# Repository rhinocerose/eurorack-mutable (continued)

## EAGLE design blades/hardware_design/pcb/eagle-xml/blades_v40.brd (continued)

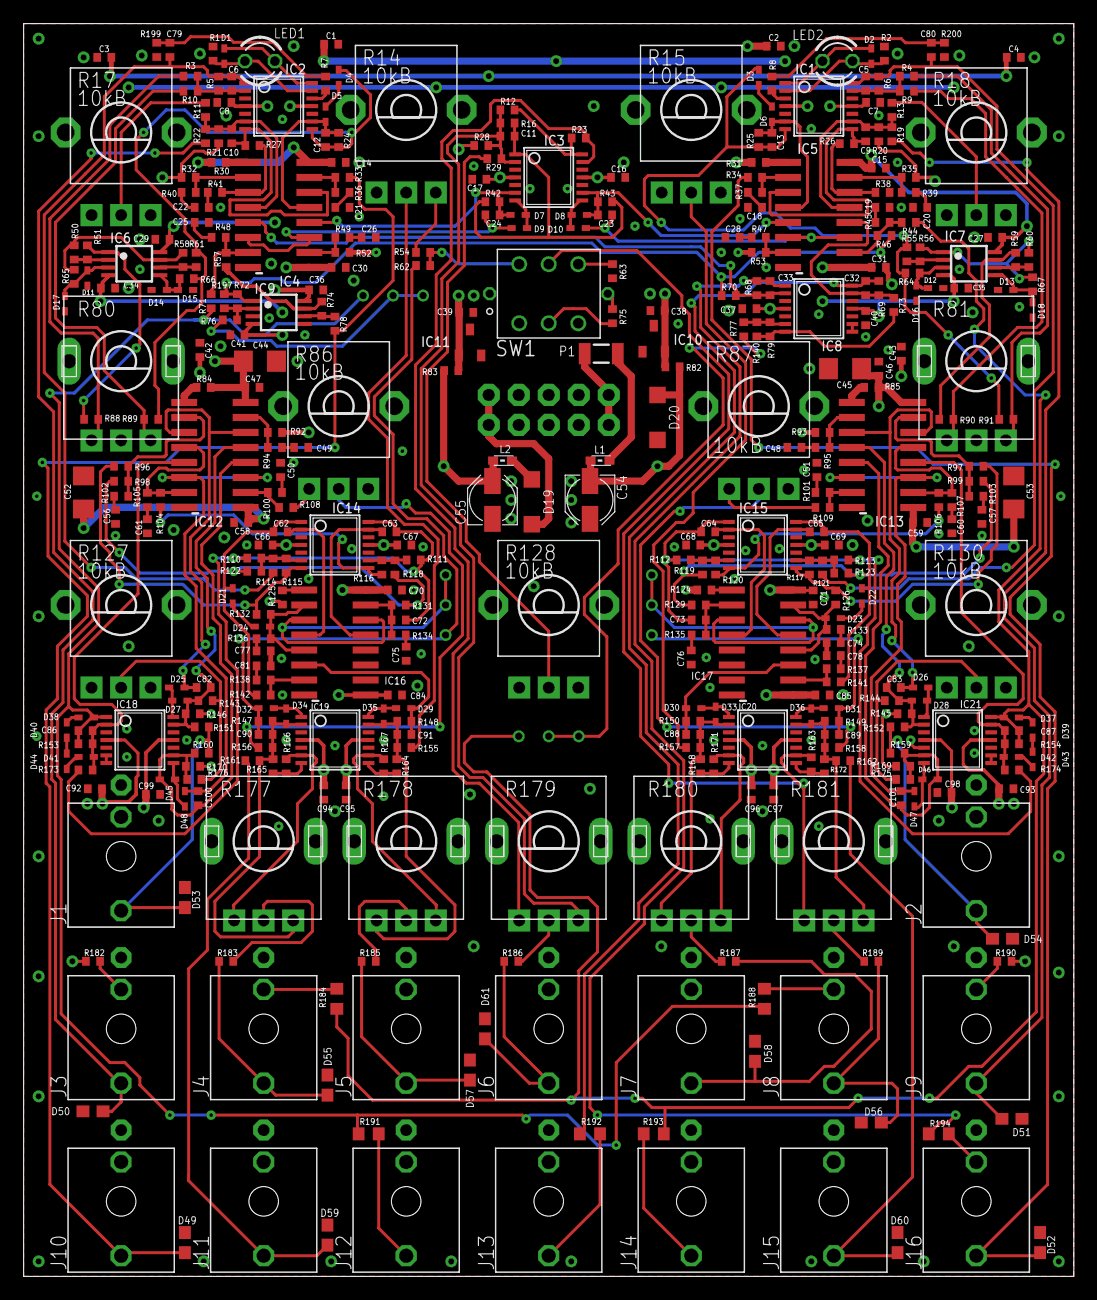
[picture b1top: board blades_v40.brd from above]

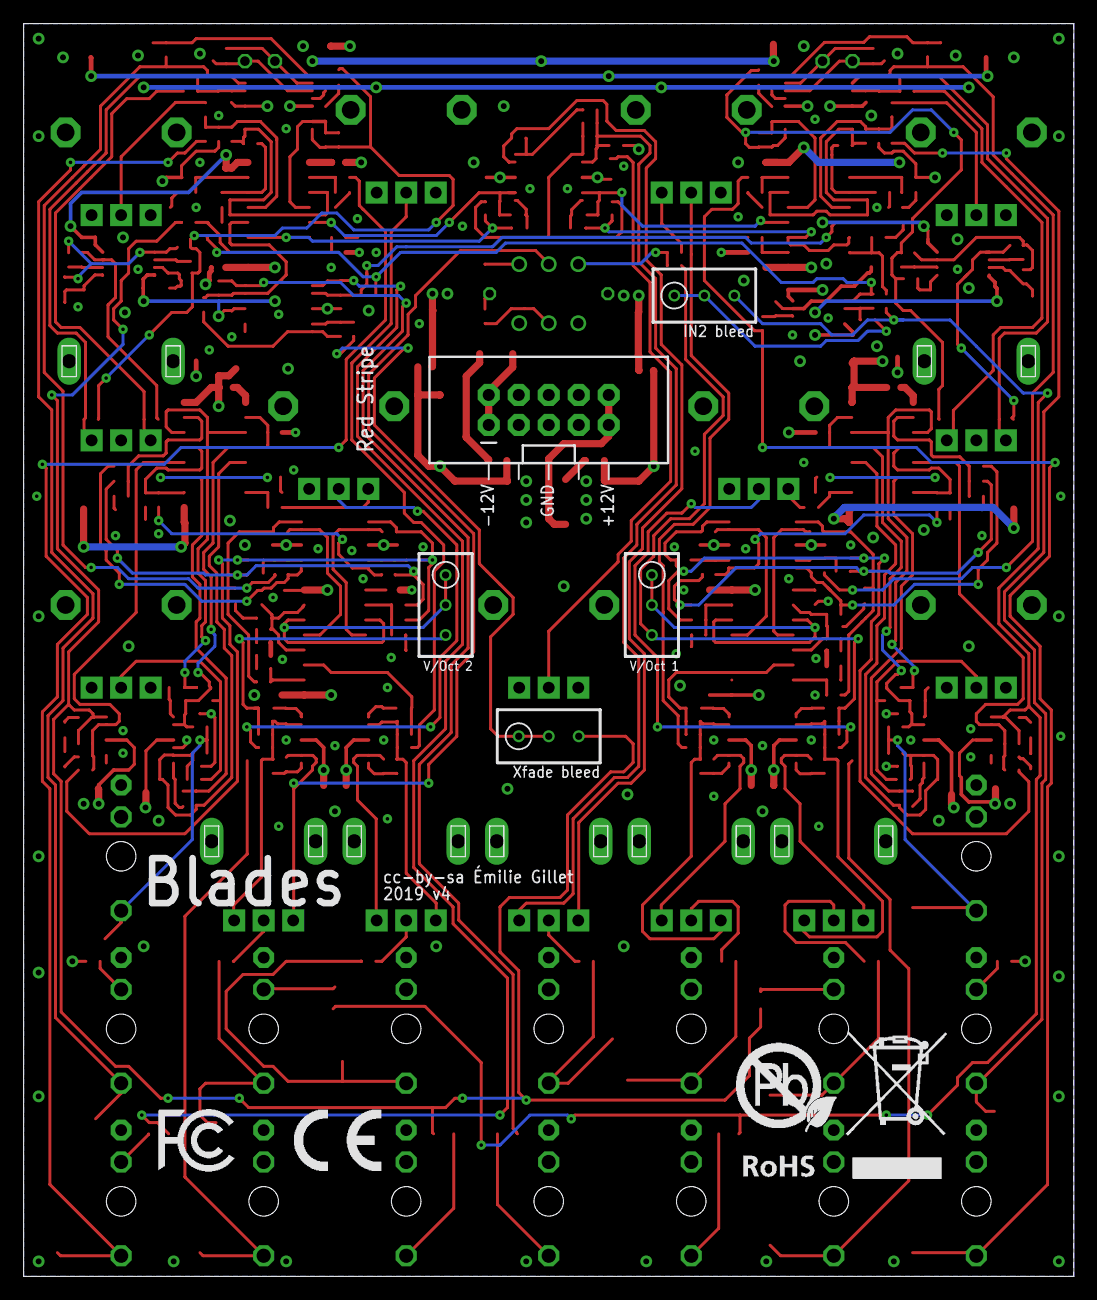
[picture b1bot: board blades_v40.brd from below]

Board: 4 copper layers, 88.9 x 106.0 mm, 409 parts (8 on the bottom side), 225 nets.

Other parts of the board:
U$1: ROHS_BIG
U$2: FCC_MEDIUM
U$3: CE_MEDIUM

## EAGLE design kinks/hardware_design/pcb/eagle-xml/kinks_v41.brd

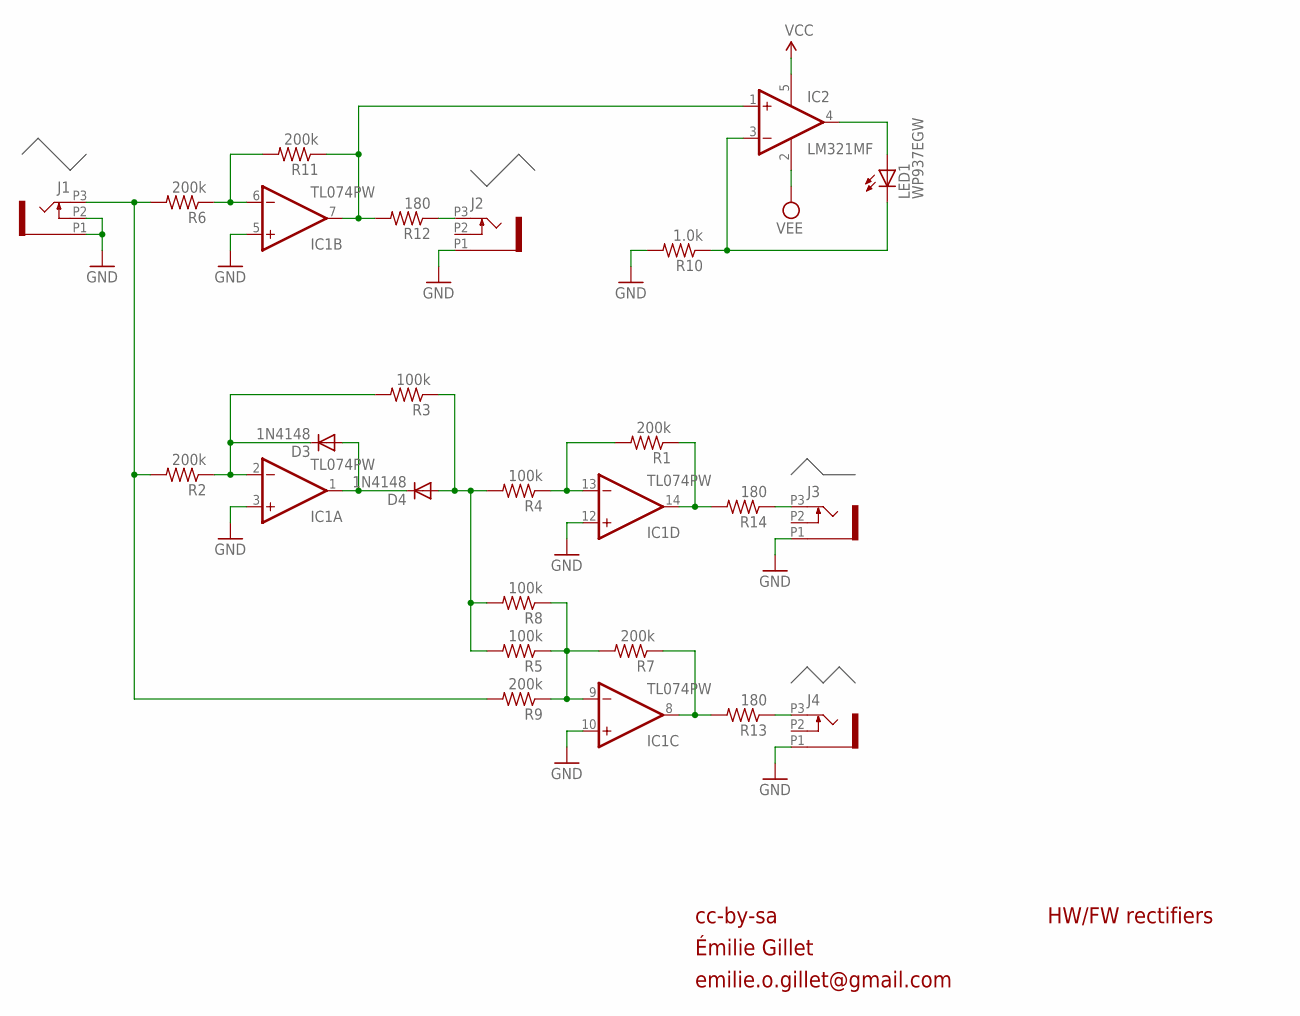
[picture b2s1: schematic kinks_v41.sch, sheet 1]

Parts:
D3, D4: 1N4148; SOD523
IC1: TL074PW; TSSOP14
IC2: LM321MF; SOT23-5
J1, J2, J3, J4: PJ301_THONKICONN6; WQP_PJ_301M6
LED1: WP937EGW; LED3MM
R1, R2, R6, R7, R9, R11: 200k; R0402
R3, R4, R5, R8: 100k; R0402
R10: 1.0k; R0402
R12, R13, R14: 180; R0402

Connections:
GND: IC1.3 (+IN), IC1.5 (+IN), IC1.10 (+IN), IC1.12 (+IN), J1.P1 (1), J1.P2 (2), J2.P1 (1), J3.P1 (1), J4.P1 (1), R10.2; also elsewhere on the board
unnamed: IC2.3 (-IN), LED1.K (C), R10.1
unnamed: IC2.4 (OUT), LED1.A
unnamed: IC1.6 (-IN), R6.1, R11.2
unnamed: IC1.7 (OUT), IC2.1 (+IN), R11.1, R12.2
unnamed: J2.P3 (3), R12.1
unnamed: D3.C, IC1.2 (-IN), R2.1, R3.2
unnamed: D3.A, D4.C, IC1.1 (OUT)
unnamed: IC1.14 (OUT), R1.1, R14.2
unnamed: IC1.13 (-IN), R1.2, R4.1
unnamed: J3.P3 (3), R14.1
unnamed: IC1.9 (-IN), R5.1, R7.2, R8.1, R9.1
unnamed: J4.P3 (3), R13.1
unnamed: IC1.8 (OUT), R7.1, R13.2
unnamed: J1.P3 (3), R2.2, R6.2, R9.2
unnamed: D4.A, R3.1, R4.2, R5.2, R8.2
VCC: IC2.5 (V+); also elsewhere on the board
VEE: IC2.2 (V-); also elsewhere on the board

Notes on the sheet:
cc-by-sa
HW/FW rectifiers
Émilie Gillet
emilie.o.gillet@gmail.com

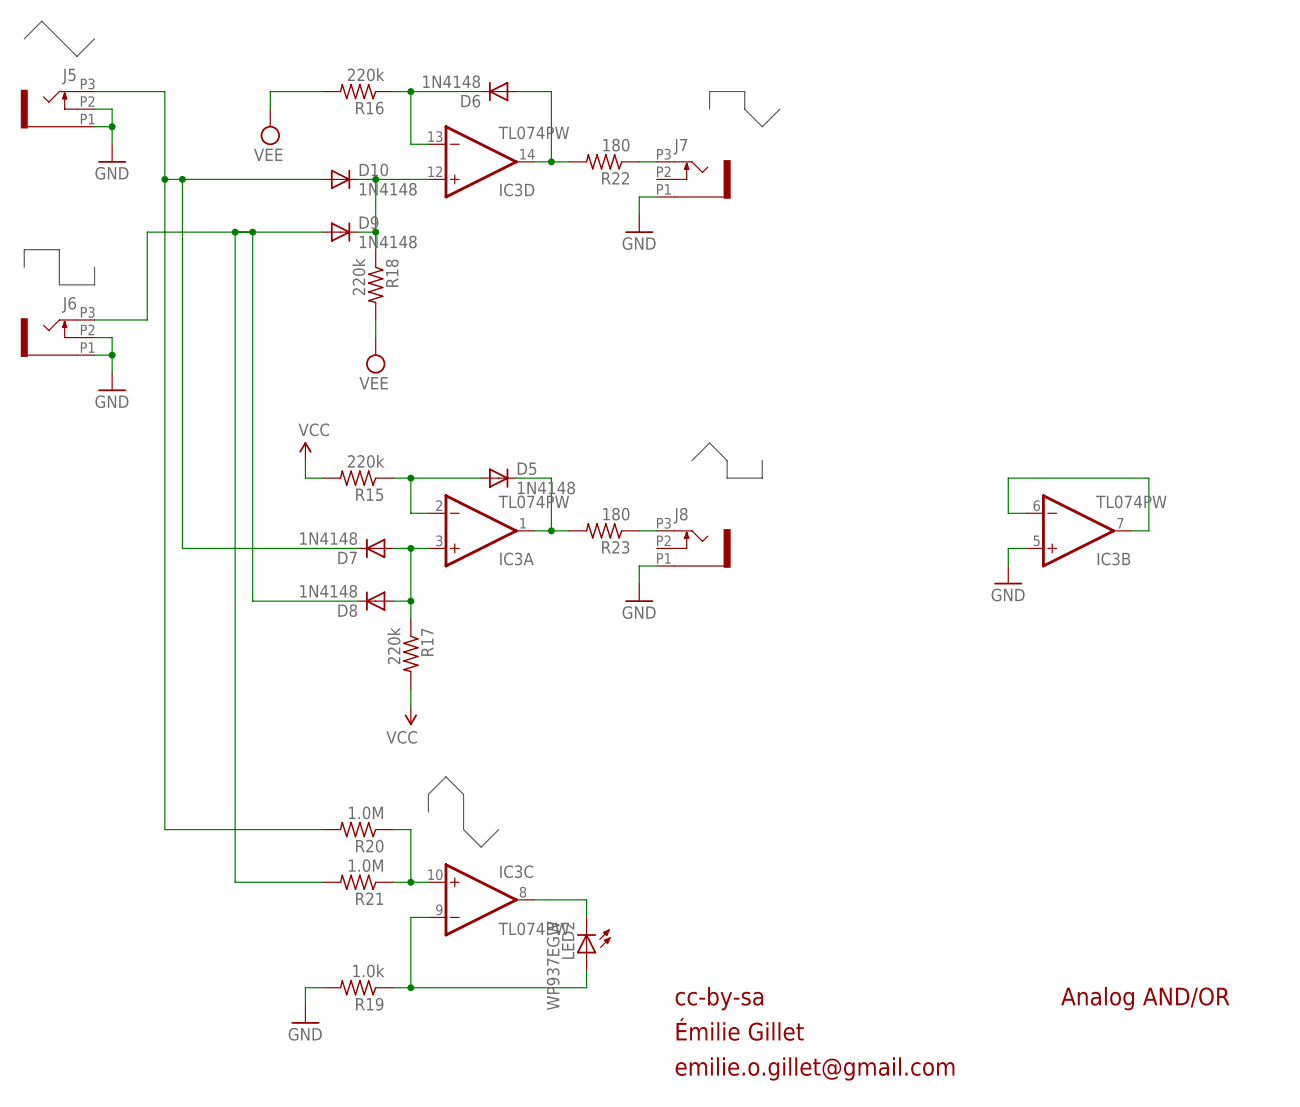
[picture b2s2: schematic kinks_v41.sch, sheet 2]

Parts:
D5, D6, D7, D8, D9, D10: 1N4148; SOD523
IC3: TL074PW; TSSOP14
J5, J6, J7, J8: PJ301_THONKICONN6; WQP_PJ_301M6
LED2: WP937EGW; LED3MM
R15, R16, R17, R18: 220k; R0402
R19: 1.0k; R0402
R20, R21: 1.0M; R0402
R22, R23: 180; R0402

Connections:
A: D7.C, D10.A, J5.P3 (3), R20.2
B: D8.C, D9.A, J6.P3 (3), R21.2
GND: IC3.5 (+IN), J5.P1 (1), J5.P2 (2), J6.P1 (1), J6.P2 (2), J7.P1 (1), J8.P1 (1), R19.2; also elsewhere on the board
unnamed: D9.C, D10.C, IC3.12 (+IN), R18.1
unnamed: D6.A, IC3.14 (OUT), R22.2
unnamed: D6.C, IC3.13 (-IN), R16.1
unnamed: D7.A, D8.A, IC3.3 (+IN), R17.1
unnamed: IC3.6 (-IN), IC3.7 (OUT)
unnamed: D5.C, IC3.1 (OUT), R23.2
unnamed: IC3.8 (OUT), LED2.K (C)
unnamed: D5.A, IC3.2 (-IN), R15.1
unnamed: J8.P3 (3), R23.1
unnamed: IC3.10 (+IN), R20.1, R21.1
unnamed: IC3.9 (-IN), LED2.A, R19.1
unnamed: J7.P3 (3), R22.1
VCC: R15.2, R17.2; also elsewhere on the board
VEE: R16.2, R18.2; also elsewhere on the board

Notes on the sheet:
cc-by-sa
Analog AND/OR
Émilie Gillet
emilie.o.gillet@gmail.com

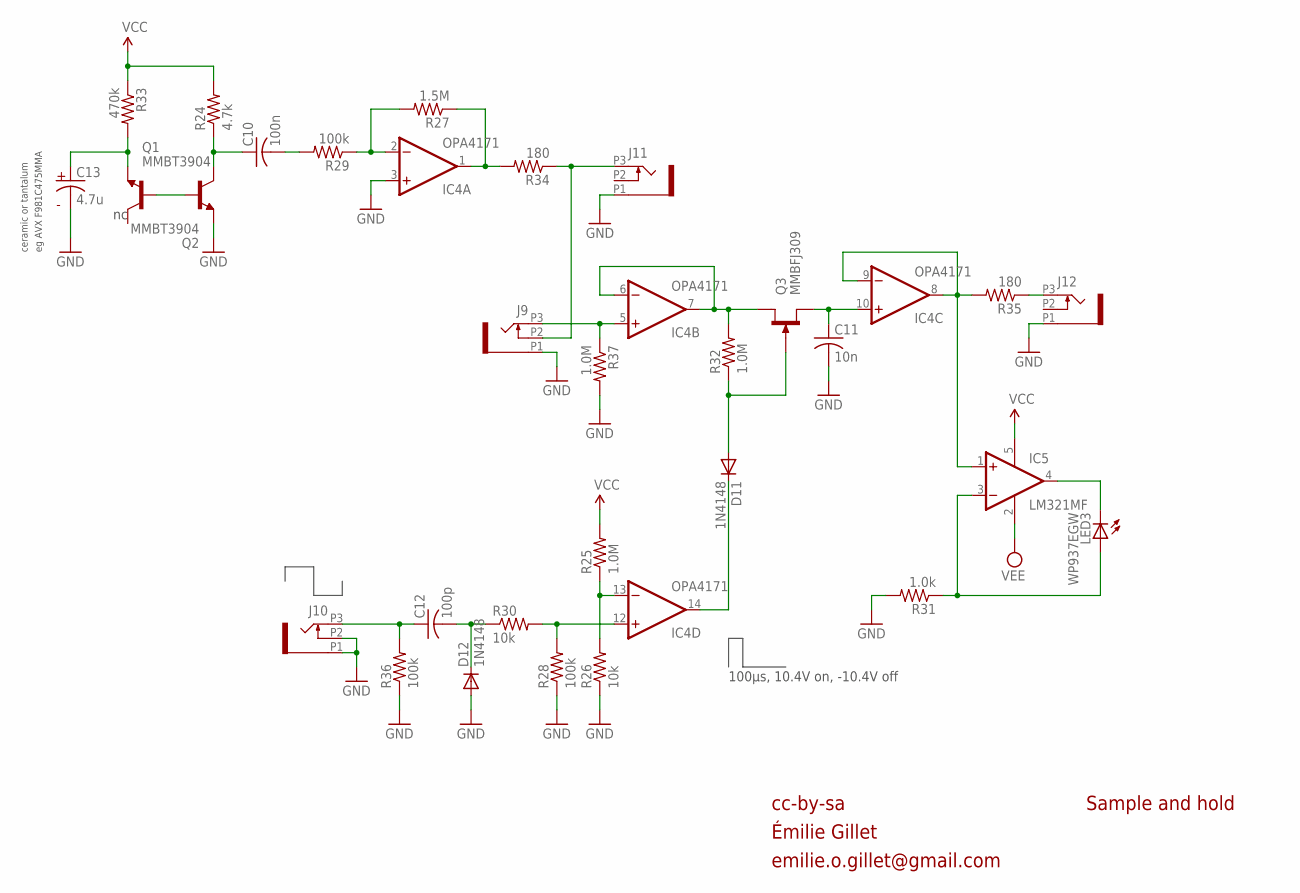
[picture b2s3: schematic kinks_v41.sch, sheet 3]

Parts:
C10: 100n; C0402
C11: 10n; C0603
C12: 100p; C0402
C13: 4.7u; C0603
D11, D12: 1N4148; SOD523
IC4: OPA4171; TSSOP14
IC5: LM321MF; SOT23-5
J9, J10, J11, J12: PJ301_THONKICONN6; WQP_PJ_301M6
LED3: WP937EGW; LED3MM
Q1, Q2: MMBT3904; SOT23-BEC
Q3: MMBFJ309; SOT23
R24: 4.7k; R0402
R25, R32, R37: 1.0M; R0402
R26, R30: 10k; R0402
R27: 1.5M; R0402
R28, R29, R36: 100k; R0402
R31: 1.0k; R0402
R33: 470k; R0402
R34, R35: 180; R0402

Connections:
GND: C11.2, C13.2, D12.A, IC4.3 (+IN), J9.P1 (1), J10.P1 (1), J10.P2 (2), J11.P1 (1), J12.P1 (1), Q1.E, R26.1, R28.1, R31.2, R36.1, R37.2; also elsewhere on the board
unnamed: IC4.8 (OUT), IC4.9 (-IN), IC5.1 (+IN), R35.2
unnamed: Q1.B, Q2.B
unnamed: C13.1, Q2.E, R33.2
unnamed: C10.2, R29.2
unnamed: IC4.2 (-IN), R27.2, R29.1
unnamed: IC5.3 (-IN), LED3.A, R31.1
unnamed: IC5.4 (OUT), LED3.K (C)
unnamed: C10.1, Q1.C, R24.1
unnamed: IC4.1 (OUT), R27.1, R34.2
unnamed: J9.P2 (2), J11.P3 (3), R34.1
unnamed: IC4.5 (+IN), J9.P3 (3), R37.1
unnamed: IC4.6 (-IN), IC4.7 (OUT), Q3.1 (D), R32.2
unnamed: D11.A, Q3.3 (G), R32.1
unnamed: D11.C, IC4.14 (OUT)
unnamed: C11.1, IC4.10 (+IN), Q3.2 (S)
unnamed: IC4.12 (+IN), R28.2, R30.2
unnamed: J12.P3 (3), R35.1
unnamed: C12.1, J10.P3 (3), R36.2
unnamed: IC4.13 (-IN), R25.1, R26.2
unnamed: C12.2, D12.C, R30.1
VCC: IC5.5 (V+), R24.2, R25.2, R33.1; also elsewhere on the board
VEE: IC5.2 (V-); also elsewhere on the board

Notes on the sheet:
cc-by-sa
Sample and hold
100µs, 10.4V on, -10.4V off
eg AVX F981C475MMA
ceramic or tantalum
Émilie Gillet
emilie.o.gillet@gmail.com

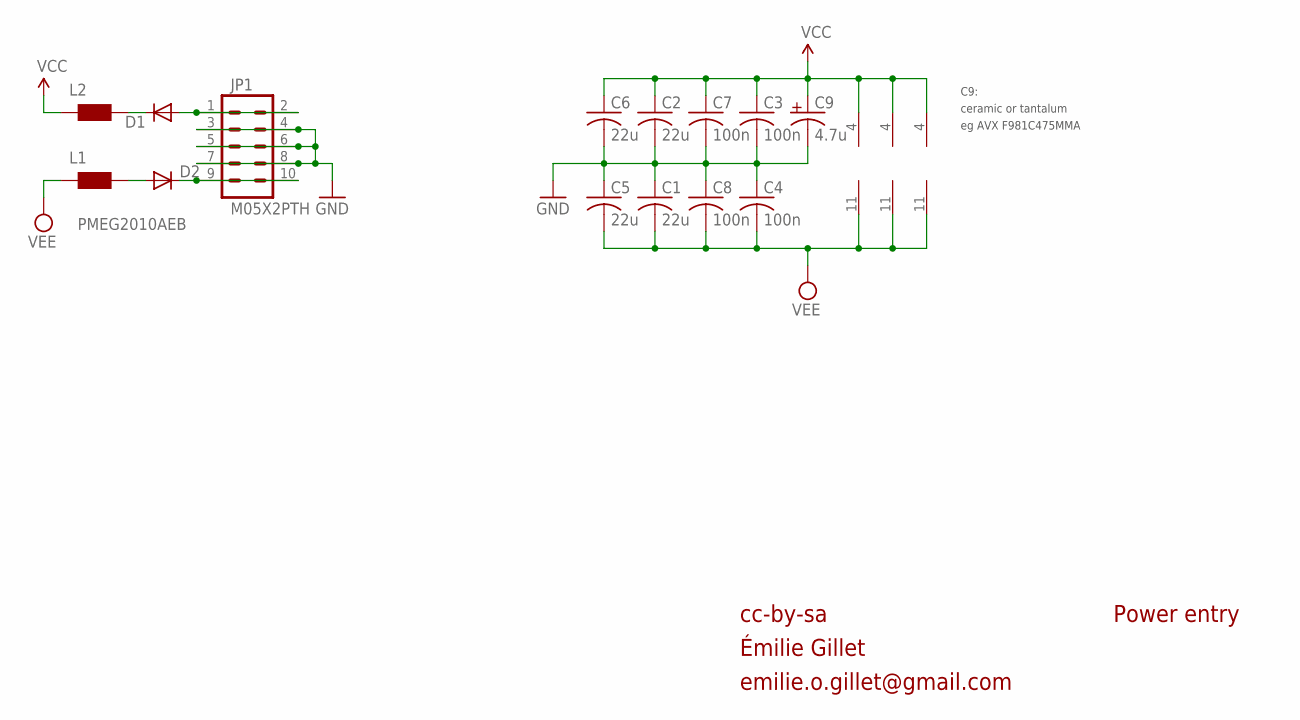
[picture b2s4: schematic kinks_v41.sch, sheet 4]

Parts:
C1, C2, C5, C6: 22u; C0805
C3, C4, C7, C8: 100n; C0402
C9: 4.7u; C0603
D1, D2: PMEG2010AEB; SOD523
IC1, IC3: TL074PW; TSSOP14
IC4: OPA4171; TSSOP14
JP1: M05X2PTH; AVR_ICSP
L1, L2: WE-CBF_0603; 0603

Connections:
GND: C1.1, C2.2, C3.2, C4.1, C5.1, C6.2, C7.2, C8.1, C9.2, JP1.3, JP1.4, JP1.5, JP1.6, JP1.7, JP1.8; also elsewhere on the board
unnamed: D1.A, JP1.1, JP1.2
unnamed: D2.C, JP1.9, JP1.10
unnamed: D1.C, L2.2
unnamed: D2.A, L1.2
VCC: C2.1, C3.1, C6.1, C7.1, C9.1, IC1.4 (V+), IC3.4 (V+), IC4.4 (V+), L2.1; also elsewhere on the board
VEE: C1.2, C4.2, C5.2, C8.2, IC1.11 (V-), IC3.11 (V-), IC4.11 (V-), L1.1; also elsewhere on the board

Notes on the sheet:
cc-by-sa
Power entry
eg AVX F981C475MMA
ceramic or tantalum
C9:
Émilie Gillet
emilie.o.gillet@gmail.com

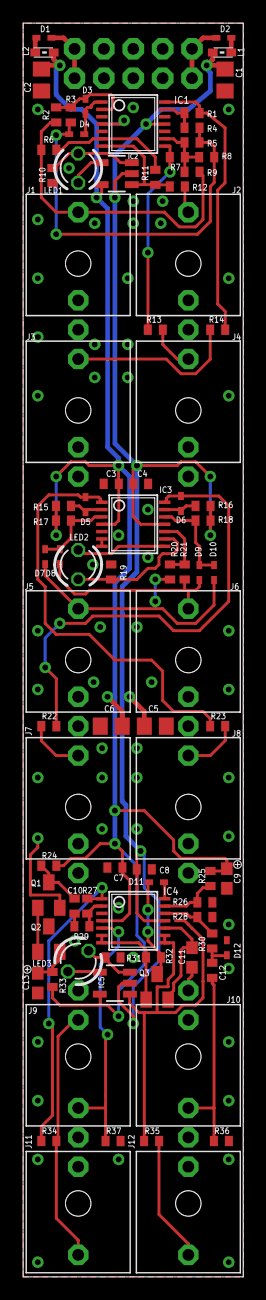
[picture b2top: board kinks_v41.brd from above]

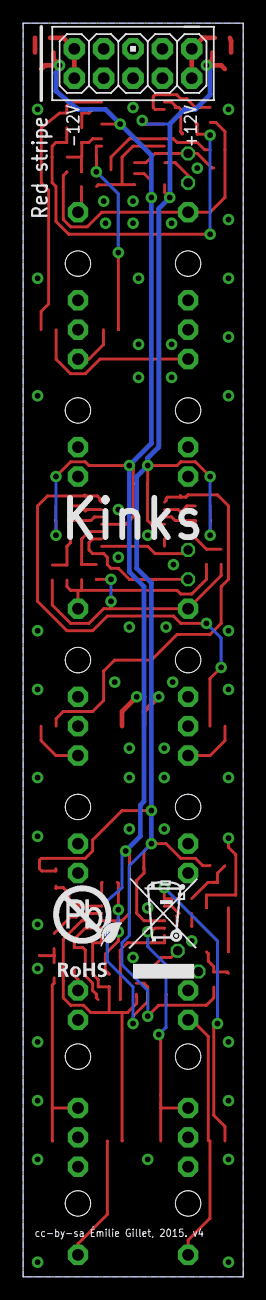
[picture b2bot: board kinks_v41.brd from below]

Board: 2 copper layers, 19.0 x 108.4 mm, 89 parts (2 on the bottom side), 56 nets.

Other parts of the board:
U$2: ROHS

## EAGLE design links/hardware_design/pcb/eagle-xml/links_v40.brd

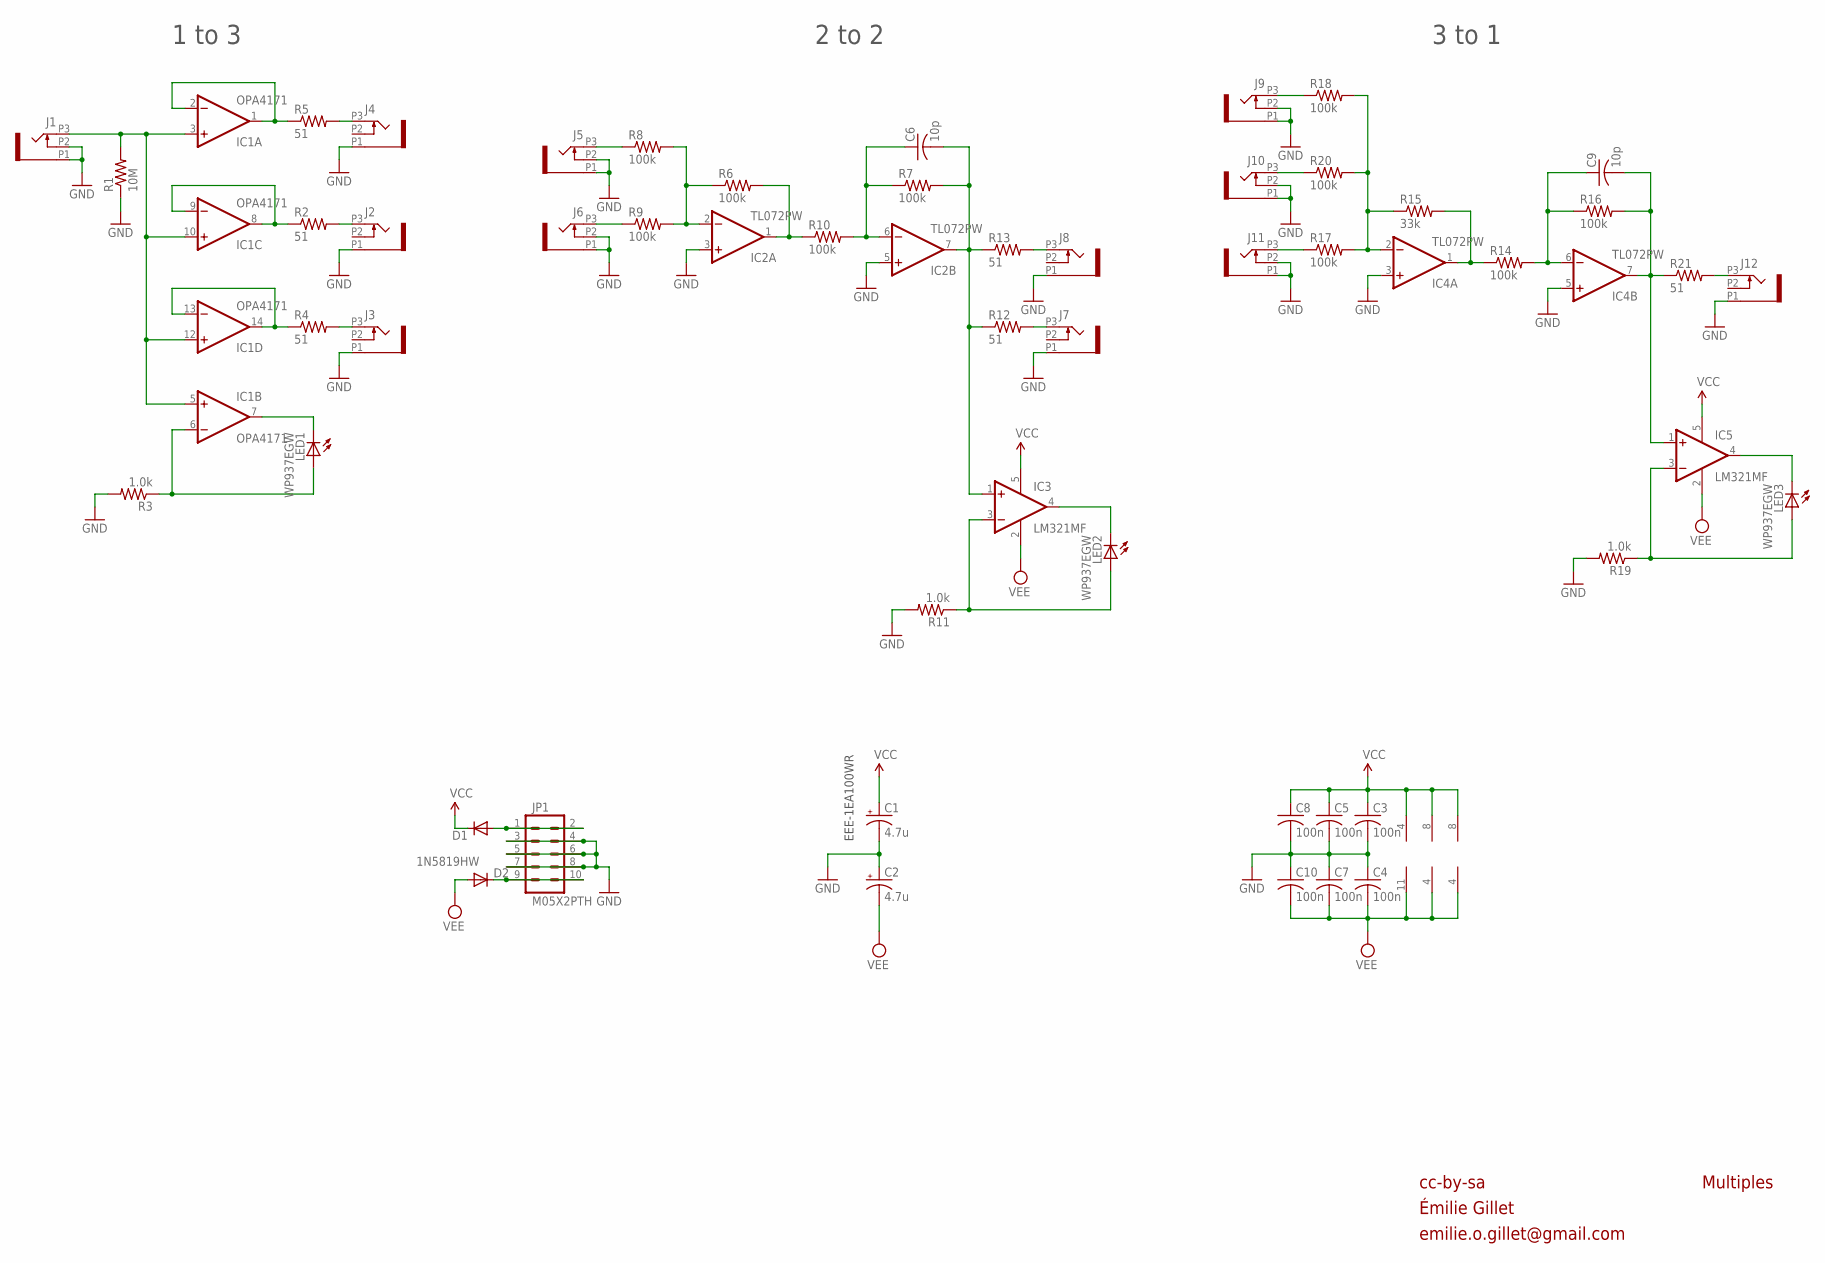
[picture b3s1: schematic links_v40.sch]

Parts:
C1, C2: 4.7u; PANASONIC_A
C3, C4, C5, C7, C8, C10: 100n; C0603
C6, C9: 10p; C0603
D1, D2: 1N5819HW; SOD123
IC1: OPA4171; TSSOP14
IC2, IC4: TL072PW; TSSOP8
IC3, IC5: LM321MF; SOT23-5
J1, J2, J3, J4, J5, J6, J7, J8, J9, J10, J11, J12: PJ301_THONKICONN6; WQP_PJ_301M6
JP1: M05X2PTH; AVR_ICSP
LED1, LED2, LED3: WP937EGW; LED3MM
R1: 10M; R0603
R2, R4, R5, R12, R13, R21: 51; R0603
R3, R11, R19: 1.0k; R0603
R6, R7, R8, R9, R10, R14, R16, R17, R18, R20: 100k; R0603
R15: 33k; R0603

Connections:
GND: C1.-, C2.+, C3.2, C4.1, C5.2, C7.1, C8.2, C10.1, IC2.3 (+IN), IC2.5 (+IN), IC4.3 (+IN), IC4.5 (+IN), J1.P1 (1), J1.P2 (2), J2.P1 (1), J3.P1 (1), J4.P1 (1), J5.P1 (1), J5.P2 (2), J6.P1 (1), J6.P2 (2), J7.P1 (1), J8.P1 (1), J9.P1 (1), J9.P2 (2), J10.P1 (1), J10.P2 (2), J11.P1 (1), J11.P2 (2), J12.P1 (1), JP1.3, JP1.4, JP1.5, JP1.6, JP1.7, JP1.8, R1.1, R3.2, R11.2, R19.2
unnamed: IC2.1 (OUT), R6.2, R10.1
unnamed: J11.P3 (3), R17.1
unnamed: IC1.1 (OUT), IC1.2 (-IN), R5.1
unnamed: IC1.8 (OUT), IC1.9 (-IN), R2.1
unnamed: IC1.13 (-IN), IC1.14 (OUT), R4.1
unnamed: D1.A, JP1.1, JP1.2
unnamed: IC1.3 (+IN), IC1.5 (+IN), IC1.10 (+IN), IC1.12 (+IN), J1.P3 (3), R1.2
unnamed: IC1.7 (OUT), LED1.K (C)
unnamed: J10.P3 (3), R20.1
unnamed: J6.P3 (3), R9.1
unnamed: J4.P3 (3), R5.2
unnamed: J2.P3 (3), R2.2
unnamed: J3.P3 (3), R4.2
unnamed: IC3.4 (OUT), LED2.K (C)
unnamed: J5.P3 (3), R8.1
unnamed: J7.P3 (3), R12.2
unnamed: J8.P3 (3), R13.2
unnamed: C9.2, IC4.7 (OUT), IC5.1 (+IN), R16.2, R21.1
unnamed: IC5.3 (-IN), LED3.A, R19.1
unnamed: D2.C, JP1.9, JP1.10
unnamed: IC1.6 (-IN), LED1.A, R3.1
unnamed: J9.P3 (3), R18.1
unnamed: J12.P3 (3), R21.2
unnamed: IC4.2 (-IN), R15.1, R17.2, R18.2, R20.2
unnamed: IC4.1 (OUT), R14.1, R15.2
unnamed: C6.2, IC2.7 (OUT), IC3.1 (+IN), R7.2, R12.1, R13.1
unnamed: C9.1, IC4.6 (-IN), R14.2, R16.1
unnamed: IC3.3 (-IN), LED2.A, R11.1
unnamed: IC5.4 (OUT), LED3.K (C)
unnamed: IC2.2 (-IN), R6.1, R8.2, R9.2
unnamed: C6.1, IC2.6 (-IN), R7.1, R10.2
VCC: C1.+, C3.1, C5.1, C8.1, D1.C, IC1.4 (V+), IC2.8 (V+), IC3.5 (V+), IC4.8 (V+), IC5.5 (V+)
VEE: C2.-, C4.2, C7.2, C10.2, D2.A, IC1.11 (V-), IC2.4 (V-), IC3.2 (V-), IC4.4 (V-), IC5.2 (V-)

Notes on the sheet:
cc-by-sa
Multiples
1 to 3
2 to 2
3 to 1
EEE-1EA100WR
Émilie Gillet
emilie.o.gillet@gmail.com

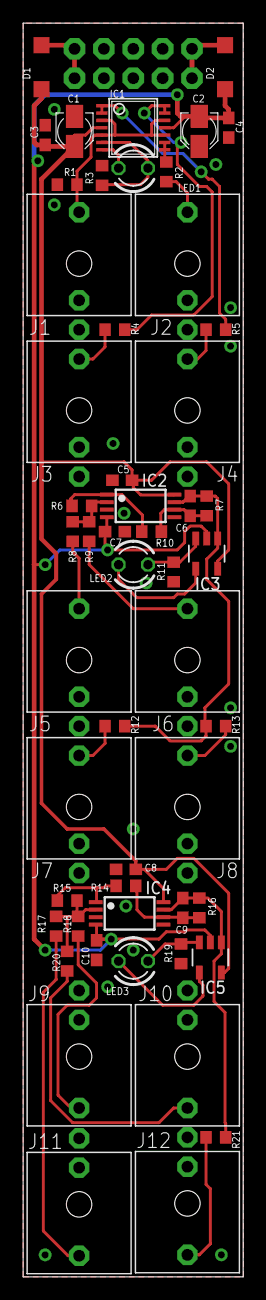
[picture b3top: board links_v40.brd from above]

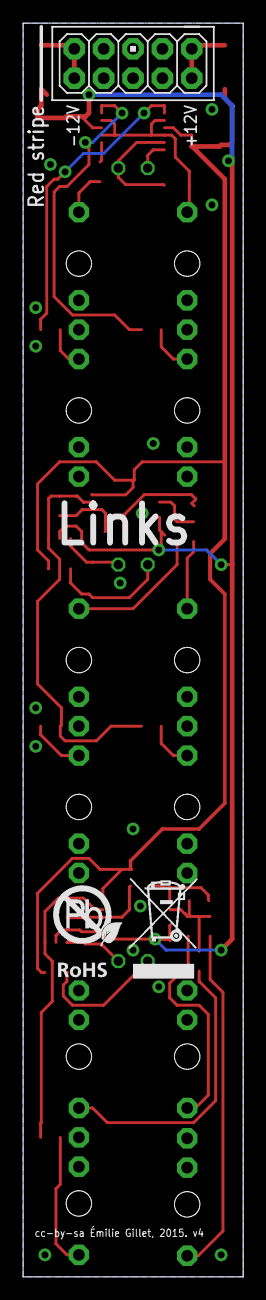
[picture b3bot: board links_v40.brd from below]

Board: 2 copper layers, 19.0 x 108.4 mm, 55 parts (2 on the bottom side), 34 nets.

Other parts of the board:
U$2: ROHS

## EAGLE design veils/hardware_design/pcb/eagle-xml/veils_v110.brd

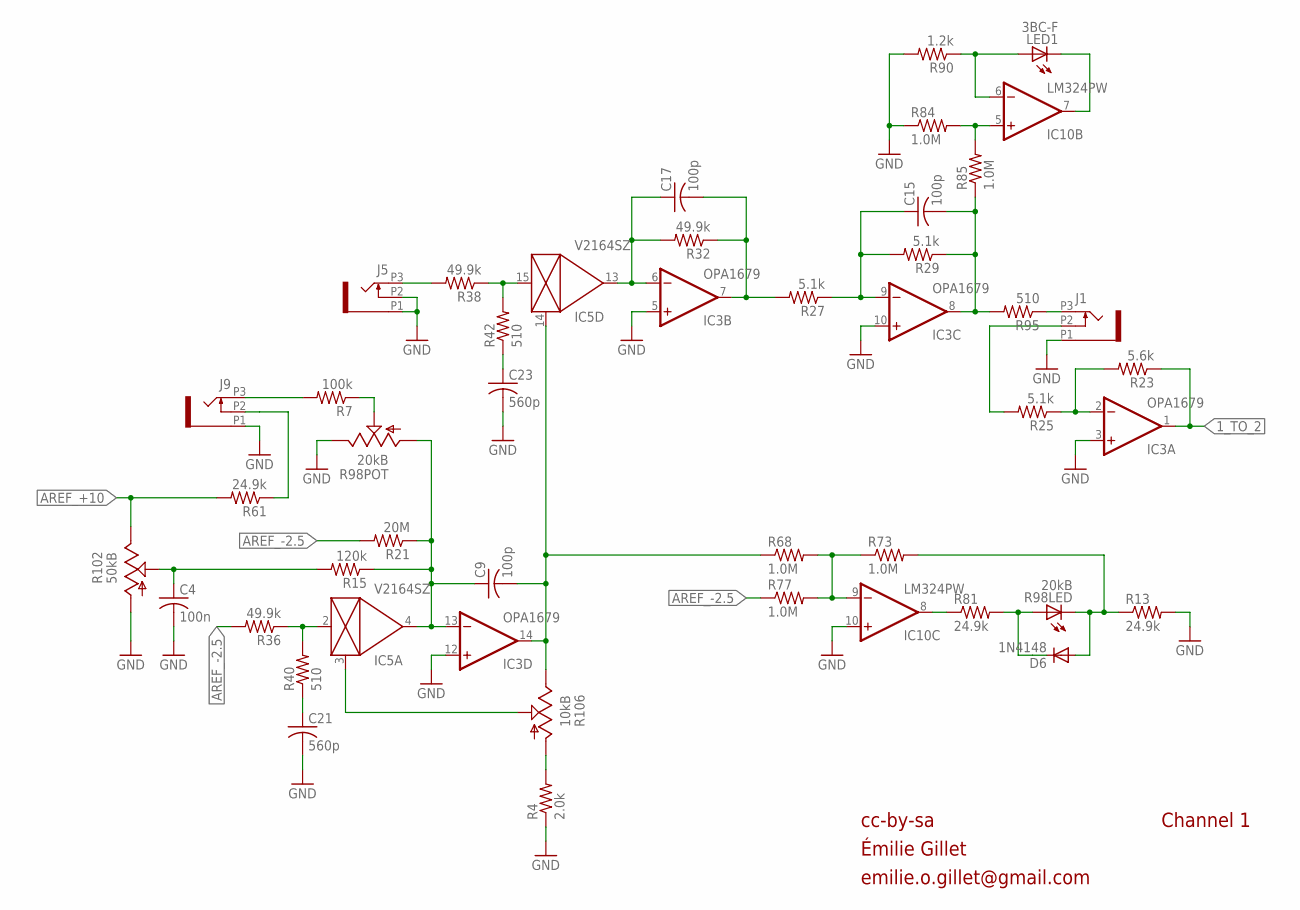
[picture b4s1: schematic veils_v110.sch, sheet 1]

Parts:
C4: 100n; C0402
C9, C15, C17: 100p; C0402
C21, C23: 560p; C0402
D6: 1N4148; SOD523
IC3: OPA1679; TSSOP14_065
IC5: V2164SZ; SOIC16N
IC10: LM324PW; TSSOP14_065
J1, J5, J9: PJ301_THONKICONNTME; WQP_PJ_301M_TME
LED1: 3BC-F; LED3MM
R4: 2.0k; R0402
R7: 100k; R0402
R13, R61, R81: 24.9k; R0402
R15: 120k; R0402
R21: 20M; R0402
R23: 5.6k; R0402
R25, R27, R29: 5.1k; R0402
R32, R36, R38: 49.9k; R0402
R40, R42: 510; R0402
R68, R73, R77, R84, R85: 1.0M; R0402
R90: 1.2k; R0402
R95: 510; R0603
R98: 20kB; BOURNS_SLIDER
R102: 50kB; ALPS_POT_NARROW
R106: 10kB; ALPS_POT_NARROW

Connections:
1_TO_2: IC3.1 (OUT), R23.1; also elsewhere on the board
AREF_+10: R61.2, R102.P$1 (E); also elsewhere on the board
AREF_-2.5: R21.2, R36.2, R77.1; also elsewhere on the board
CV_IN_1: J9.P3 (3), R7.2
FOO: IC5.2 (IN), R36.1, R40.2
GND: C4.2, C21.2, C23.2, IC3.3 (+IN), IC3.5 (+IN), IC3.10 (+IN), IC3.12 (+IN), IC10.10 (+IN), J1.P1 (1), J5.P1 (1), J5.P2 (2), J9.P1 (1), R4.1, R13.2, R84.1, R90.2, R98.3 (E), R102.P$3 (A); also elsewhere on the board
unnamed: IC10.5 (+IN), R84.2, R85.2
unnamed: J1.P3 (3), R95.1
unnamed: IC5.3 (CTRL), R106.P$2 (S)
unnamed: C15.1, IC3.9 (-IN), R27.1, R29.2
unnamed: C4.1, R15.2, R102.P$2 (S)
unnamed: R4.2, R106.P$3 (A)
unnamed: IC10.7 (OUT), LED1.K (C)
unnamed: IC10.6 (-IN), LED1.A, R90.1
unnamed: C21.1, R40.1
unnamed: IC3.2 (-IN), R23.2, R25.1
unnamed: J1.P2 (2), R25.2
unnamed: J9.P2 (2), R61.1
unnamed: R7.1, R98.2 (S)
unnamed: C23.1, R42.1
unnamed: IC10.8 (OUT), R81.1
unnamed: D6.A, R13.1, R73.2, R98.E (C)
unnamed: IC10.9 (-IN), R68.2, R73.1, R77.2
unnamed: C9.1, IC3.13 (-IN), IC5.4 (OUT), R15.1, R21.1, R98.1 (A)
unnamed: J5.P3 (3), R38.2
unnamed: IC5.15 (IN), R38.1, R42.2
unnamed: C9.2, IC3.14 (OUT), IC5.14 (CTRL), R68.1, R106.P$1 (E)
unnamed: C17.1, IC3.6 (-IN), IC5.13 (OUT), R32.2
unnamed: C17.2, IC3.7 (OUT), R27.2, R32.1
OUT1: C15.2, IC3.8 (OUT), R29.1, R85.1, R95.2
PROT1: D6.C, R81.2, R98.B (A)

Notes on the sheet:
cc-by-sa
Channel 1
Émilie Gillet
emilie.o.gillet@gmail.com

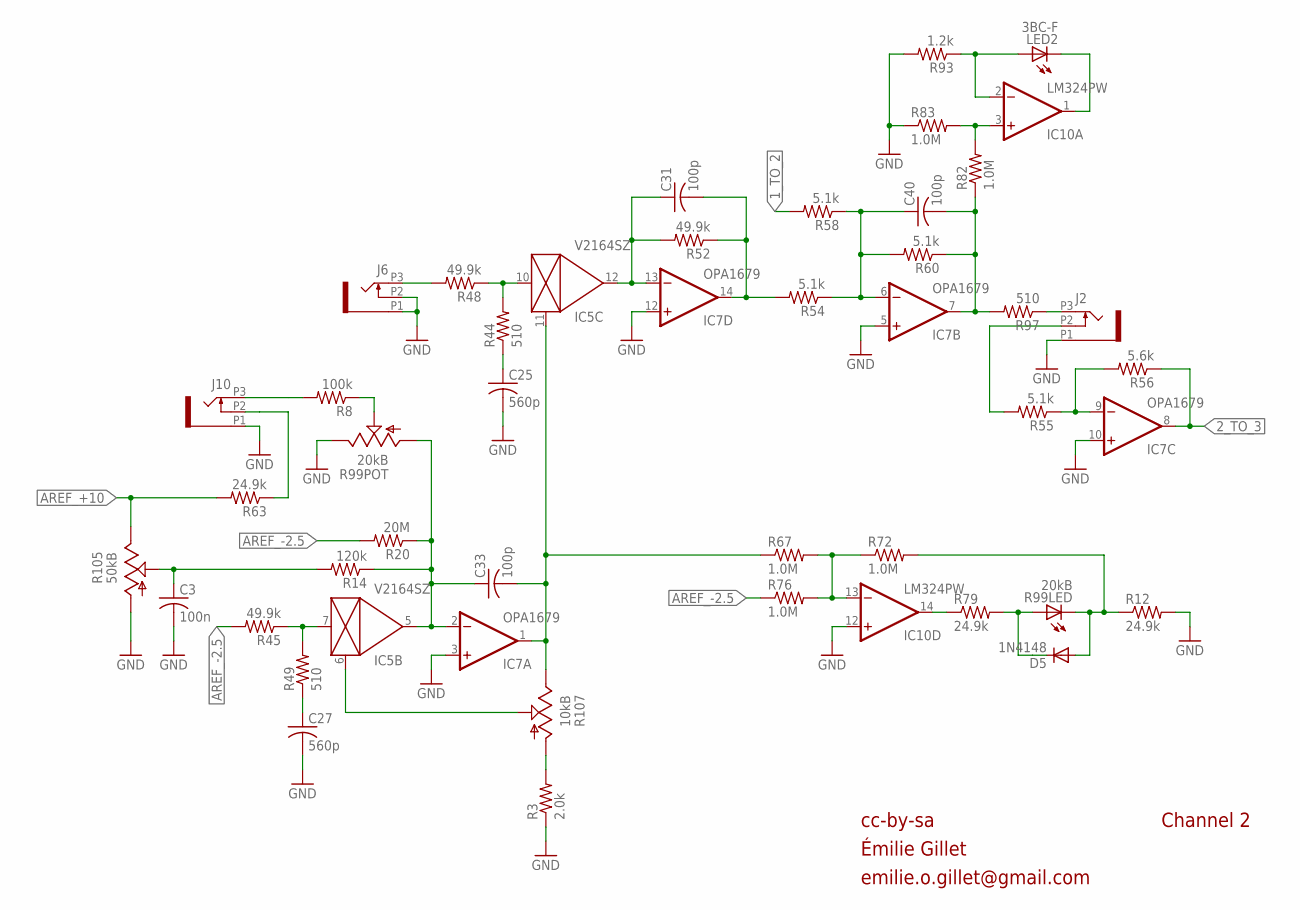
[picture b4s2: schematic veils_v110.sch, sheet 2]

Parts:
C3: 100n; C0402
C25, C27: 560p; C0402
C31, C33, C40: 100p; C0402
D5: 1N4148; SOD523
IC5: V2164SZ; SOIC16N
IC7: OPA1679; TSSOP14_065
IC10: LM324PW; TSSOP14_065
J2, J6, J10: PJ301_THONKICONNTME; WQP_PJ_301M_TME
LED2: 3BC-F; LED3MM
R3: 2.0k; R0402
R8: 100k; R0402
R12, R63, R79: 24.9k; R0402
R14: 120k; R0402
R20: 20M; R0402
R44, R49: 510; R0402
R45, R48, R52: 49.9k; R0402
R54, R55, R58, R60: 5.1k; R0402
R56: 5.6k; R0402
R67, R72, R76, R82, R83: 1.0M; R0402
R93: 1.2k; R0402
R97: 510; R0603
R99: 20kB; BOURNS_SLIDER
R105: 50kB; ALPS_POT_NARROW
R107: 10kB; ALPS_POT_NARROW

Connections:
1_TO_2: R58.2; also elsewhere on the board
2_TO_3: IC7.8 (OUT), R56.1; also elsewhere on the board
AREF_+10: R63.2, R105.P$1 (E); also elsewhere on the board
AREF_-2.5: R20.2, R45.2, R76.1; also elsewhere on the board
FOO1: IC5.7 (IN), R45.1, R49.2
GND: C3.2, C25.2, C27.2, IC7.3 (+IN), IC7.5 (+IN), IC7.10 (+IN), IC7.12 (+IN), IC10.12 (+IN), J2.P1 (1), J6.P1 (1), J6.P2 (2), J10.P1 (1), R3.1, R12.2, R83.1, R93.2, R99.3 (E), R105.P$3 (A); also elsewhere on the board
unnamed: J6.P3 (3), R48.2
unnamed: IC10.3 (+IN), R82.2, R83.2
unnamed: J2.P3 (3), R97.1
unnamed: C25.1, R44.1
unnamed: J10.P2 (2), R63.1
unnamed: IC5.10 (IN), R44.2, R48.1
unnamed: IC5.6 (CTRL), R107.P$2 (S)
unnamed: C40.1, IC7.6 (-IN), R54.1, R58.1, R60.2
unnamed: R3.2, R107.P$3 (A)
unnamed: R8.1, R99.2 (S)
unnamed: IC10.1 (OUT), LED2.K (C)
unnamed: IC10.2 (-IN), LED2.A, R93.1
unnamed: IC7.9 (-IN), R55.1, R56.2
unnamed: J2.P2 (2), R55.2
unnamed: C31.2, IC7.14 (OUT), R52.1, R54.2
unnamed: J10.P3 (3), R8.2
unnamed: C27.1, R49.1
unnamed: C33.1, IC5.5 (OUT), IC7.2 (-IN), R14.1, R20.1, R99.1 (A)
unnamed: C31.1, IC5.12 (OUT), IC7.13 (-IN), R52.2
unnamed: D5.A, R12.1, R72.2, R99.E (C)
unnamed: IC10.14 (OUT), R79.1
unnamed: IC10.13 (-IN), R67.2, R72.1, R76.2
unnamed: C33.2, IC5.11 (CTRL), IC7.1 (OUT), R67.1, R107.P$1 (E)
unnamed: C3.1, R14.2, R105.P$2 (S)
OUT2: C40.2, IC7.7 (OUT), R60.1, R82.1, R97.2
PROT2: D5.C, R79.2, R99.B (A)

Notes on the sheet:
cc-by-sa
Émilie Gillet
emilie.o.gillet@gmail.com
Channel 2
